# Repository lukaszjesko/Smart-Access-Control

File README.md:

# Smart Access Control

A door lock controller on my own PCB. To open the door you need the right RFID card
and the right 4-digit PIN. An Arduino Nano checks both and switches a 12 V door strike
through a relay.

| KiCad 3D render | Assembled board |
|---|---|
|  |  |

This is the first PCB I designed and ordered. I drew v1.0 in KiCad, found a lot of
mistakes during a review, fixed them in v1.1 and ordered v1.1 from JLCPCB.

## What's on the board

Arduino Nano, MFRC522 RFID reader (as a module on a header), 4x4 keypad, 16x2 LCD over
I2C, relay module, buzzer and two LEDs.

The firmware is a simple state machine: wait for a card, wait for the PIN, open or deny,
then back to waiting.

| Routing (ground pour hidden) | All copper layers |
|---|---|
|  |  |

*Red = top copper, blue = bottom copper. On the left the ground pour is hidden so
the tracks are visible.*

Schematic as PDF: [docs/schematic_v1.1.pdf](docs/schematic_v1.1.pdf).
KiCad project: [Zamek_RFID_Hardware/](Zamek_RFID_Hardware/Zamek_RFID_Hardware).

## Mistakes in v1.0 that I fixed in v1.1

- Both LEDs were wired backwards, so they could never light up.
- There were no decoupling capacitors. I had a supply dip that I worked around in
  firmware, but the real problem was in hardware.
- Every track was 0.25 mm, including power. Now power tracks are 0.6 mm and there is
  a ground pour on both layers.
- The Nano sent 5 V signals into the 3.3 V RFID reader. Now there are 1k/2k resistor
  dividers on MOSI, SCK and SS.
- The buzzer was driven straight from a pin. Now it goes through a BC547 transistor
  with a flyback diode.
- No mounting holes and no test points. Now there are four M3 holes and test points on
  5 V, 3.3 V and GND.

## A bug I liked

The relay module is active LOW, so at power-up the door opened for a split second
before the program set the pin. Writing HIGH to the pin before `pinMode()` fixed it.

## Not done yet

- Assemble and test v1.1
- Firmware: replace `String` with a `char` buffer, replace `delay()` with `millis()`,
  lock the keypad after 5 wrong PINs
- Security: only the card UID is checked, and a UID can be copied to a cheap card.
  The PIN is stored in the firmware as plain text.

## Build

PlatformIO, target `nanoatmega328new`:

```bash
cp include/config.example.h include/config.h   # set your card UID and PIN
pio run --target upload
```

## License

Firmware: [MIT](LICENSE). Hardware: [CERN-OHL-S-2.0](LICENSE-HARDWARE).

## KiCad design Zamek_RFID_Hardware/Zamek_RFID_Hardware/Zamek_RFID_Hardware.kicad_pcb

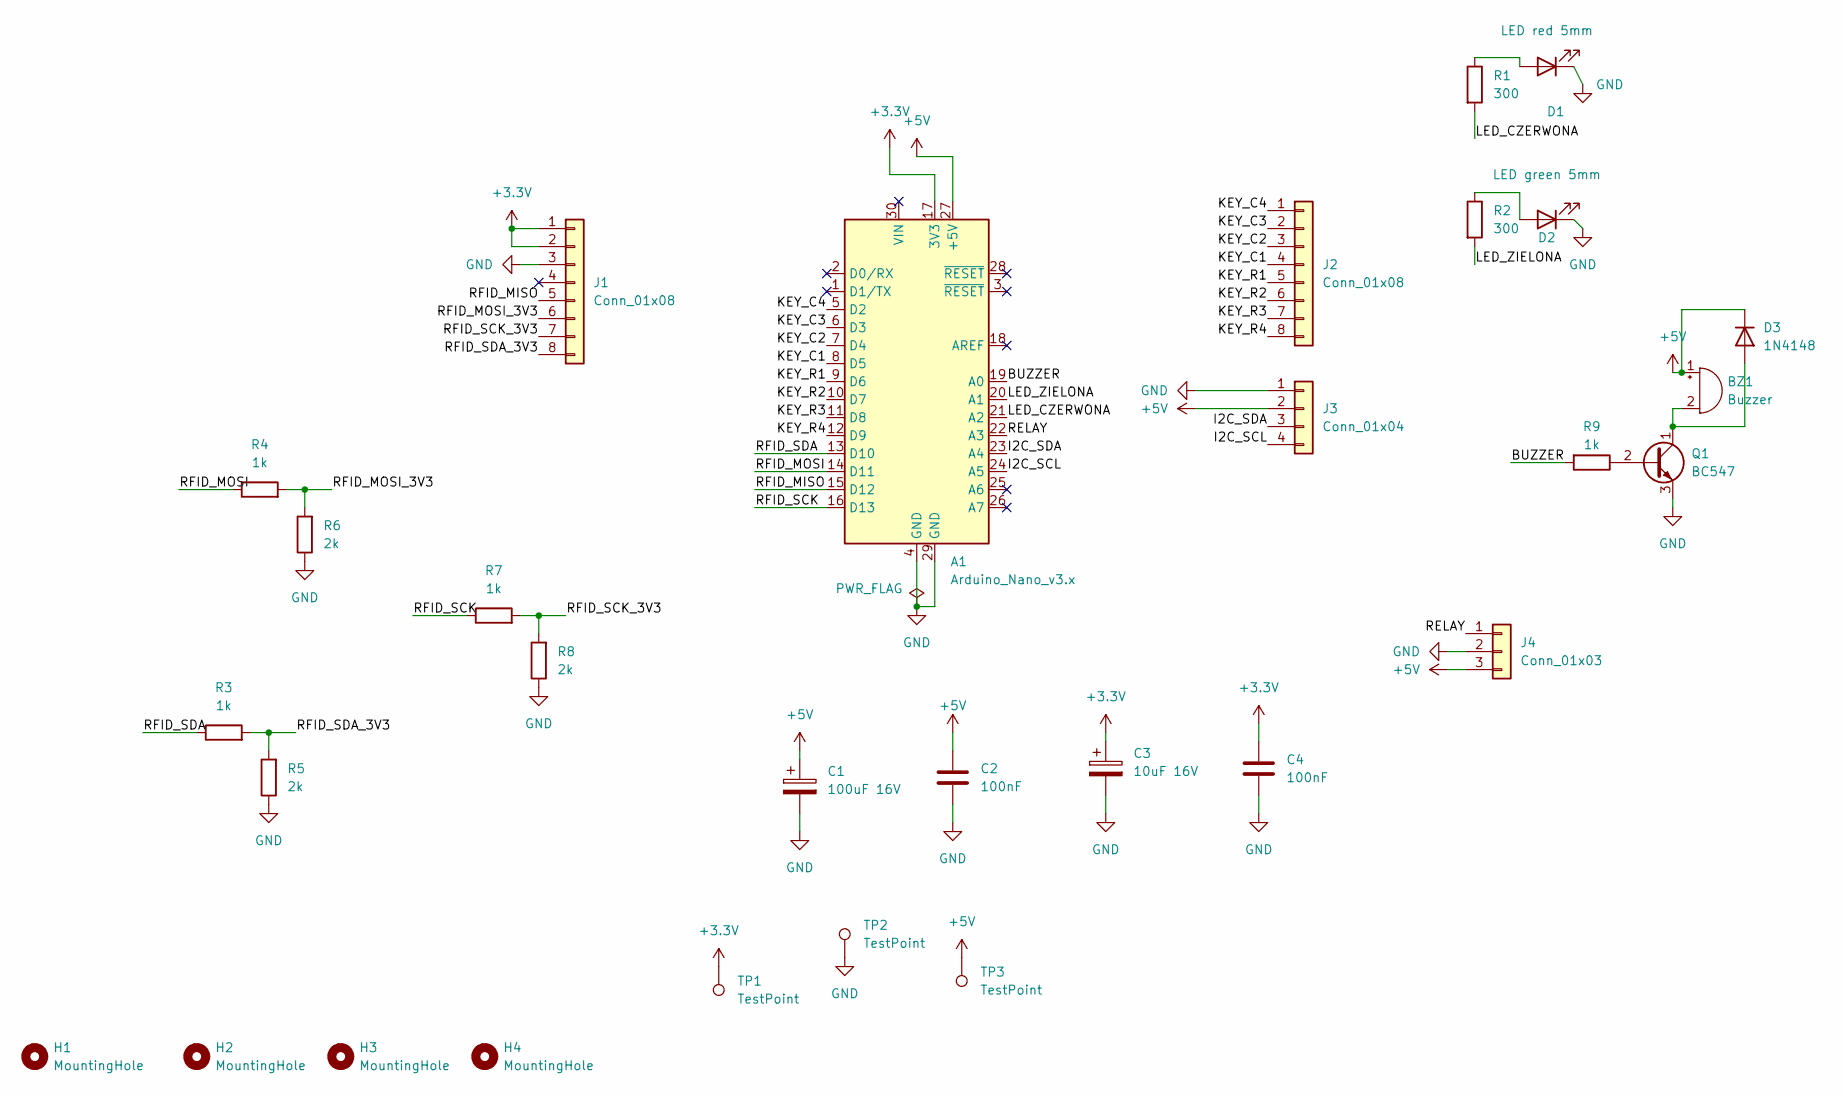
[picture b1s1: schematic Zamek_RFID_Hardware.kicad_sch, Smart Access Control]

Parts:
A1: Arduino_Nano_v3.x; Arduino_Nano
BZ1: Buzzer; Buzzer_12x9.5RM7.6
C1: 100uF 16V; CP_Radial_D6.3mm_P2.50mm
C2, C4: 100nF; C_Disc_D5.0mm_W2.5mm_P5.00mm
C3: 10uF 16V; CP_Radial_D5.0mm_P2.00mm
D1: LED red 5mm; LED_D5.0mm
D2: LED green 5mm; LED_D5.0mm
D3: 1N4148; D_DO-35_SOD27_P7.62mm_Horizontal
H1, H2, H3, H4: MountingHole; MountingHole_3.2mm_M3
J1, J2: Conn_01x08; PinHeader_1x08_P2.54mm_Vertical
J3: Conn_01x04; PinHeader_1x04_P2.54mm_Vertical
J4: Conn_01x03; PinHeader_1x03_P2.54mm_Vertical
Q1: BC547; TO-92_Inline
R1, R2: 300; R_Axial_DIN0207_L6.3mm_D2.5mm_P10.16mm_Horizontal
R3, R4, R7, R9: 1k; R_Axial_DIN0207_L6.3mm_D2.5mm_P10.16mm_Horizontal
R5, R6, R8: 2k; R_Axial_DIN0207_L6.3mm_D2.5mm_P10.16mm_Horizontal
TP1, TP2, TP3: TestPoint; TestPoint_THTPad_D2.0mm_Drill1.0mm

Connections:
+3.3V: A1.17 (3V3), C3.1, C4.1, J1.1, J1.2, TP1.1 (1_1)
+5V: A1.27 (+5V), BZ1.1 (+), C1.1, C2.1, D3.1 (K), J3.2, J4.3, TP3.1 (1_1)
/BUZZER: A1.19 (A0), R9.2
/I2C_SCL: A1.24 (A5), J3.4
/I2C_SDA: A1.23 (A4), J3.3
/KEY_C1: A1.8 (D5), J2.4
/KEY_C2: A1.7 (D4), J2.3
/KEY_C3: A1.6 (D3), J2.2
/KEY_C4: A1.5 (D2), J2.1
/KEY_R1: A1.9 (D6), J2.5
/KEY_R2: A1.10 (D7), J2.6
/KEY_R3: A1.11 (D8), J2.7
/KEY_R4: A1.12 (D9), J2.8
/LED_CZERWONA: A1.21 (A2), R1.2
/LED_ZIELONA: A1.20 (A1), R2.2
/RELAY: A1.22 (A3), J4.1
/RFID_MISO: A1.15 (D12), J1.5
/RFID_MOSI: A1.14 (D11), R4.1
/RFID_MOSI_3V3: J1.6, R4.2, R6.2
/RFID_SCK: A1.16 (D13), R7.1
/RFID_SCK_3V3: J1.7, R7.2, R8.2
/RFID_SDA: A1.13 (D10), R3.1
/RFID_SDA_3V3: J1.8, R3.2, R5.2
GND: A1.4 (GND), A1.29 (GND), C1.2, C2.2, C3.2, C4.2, D1.1 (K), D2.1 (K), J1.3, J3.1, J4.2, Q1.3 (E), R5.1, R6.1, R8.1, TP2.1 (1_1)
unnamed: BZ1.2 (-), D3.2 (A), Q1.1 (C)
unnamed: D1.2 (A), R1.1
unnamed: D2.2 (A), R2.1
unnamed: Q1.2 (B), R9.1

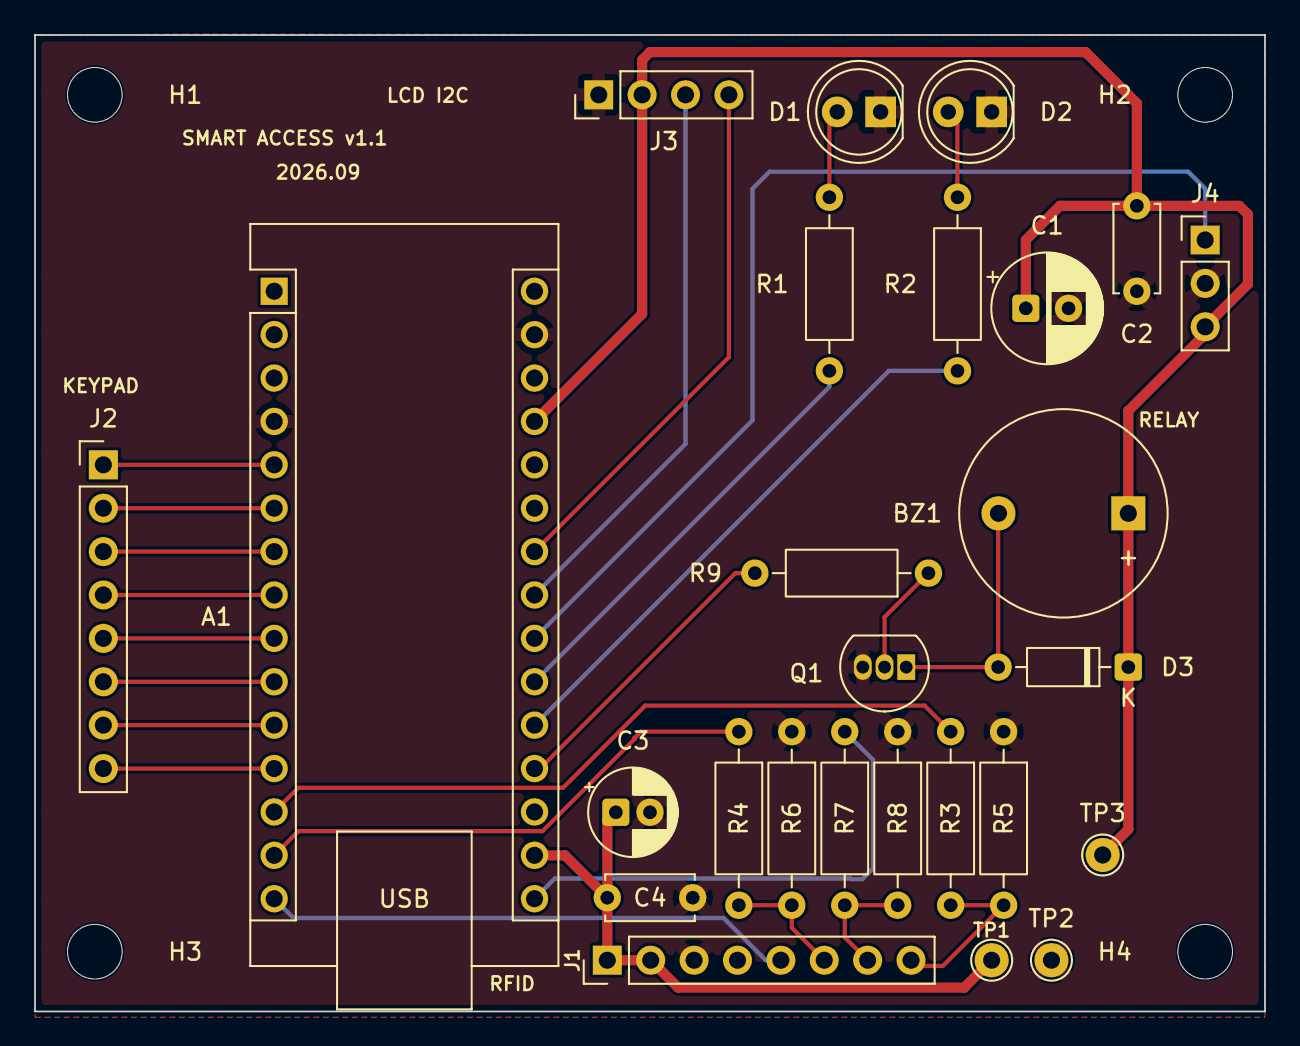
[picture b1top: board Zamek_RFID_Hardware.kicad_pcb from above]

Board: 2 copper layers, 72.0 x 57.2 mm, 30 parts (0 on the bottom side), 28 nets.

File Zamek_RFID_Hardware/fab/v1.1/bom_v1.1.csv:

"Reference","Value","Datasheet","Footprint","Qty","DNP"
"A1","Arduino_Nano_v3.x","http://www.mouser.com/pdfdocs/Gravitech_Arduino_Nano3_0.pdf","Module:Arduino_Nano","1",""
"BZ1","Buzzer","","Buzzer_Beeper:Buzzer_12x9.5RM7.6","1",""
"C1","100uF 16V","","Capacitor_THT:CP_Radial_D6.3mm_P2.50mm","1",""
"C2,C4","100nF","","Capacitor_THT:C_Disc_D5.0mm_W2.5mm_P5.00mm","2",""
"C3","10uF 16V","","Capacitor_THT:CP_Radial_D5.0mm_P2.00mm","1",""
"D1","LED red 5mm","","LED_THT:LED_D5.0mm","1",""
"D2","LED green 5mm","","LED_THT:LED_D5.0mm","1",""
"D3","1N4148","https://assets.nexperia.com/documents/data-sheet/1N4148_1N4448.pdf","Diode_THT:D_DO-35_SOD27_P7.62mm_Horizontal","1",""
"J1,J2","Conn_01x08","","Connector_PinHeader_2.54mm:PinHeader_1x08_P2.54mm_Vertical","2",""
"J3","Conn_01x04","","Connector_PinHeader_2.54mm:PinHeader_1x04_P2.54mm_Vertical","1",""
"J4","Conn_01x03","","Connector_PinHeader_2.54mm:PinHeader_1x03_P2.54mm_Vertical","1",""
"Q1","BC547","https://www.onsemi.com/pub/Collateral/BC550-D.pdf","Package_TO_SOT_THT:TO-92_Inline","1",""
"R1","300","","Resistor_THT:R_Axial_DIN0207_L6.3mm_D2.5mm_P10.16mm_Horizontal","1",""
"R2","200","","Resistor_THT:R_Axial_DIN0207_L6.3mm_D2.5mm_P10.16mm_Horizontal","1",""
"R3,R4,R7,R9","1k","","Resistor_THT:R_Axial_DIN0207_L6.3mm_D2.5mm_P10.16mm_Horizontal","4",""
"R5,R6,R8","2k","","Resistor_THT:R_Axial_DIN0207_L6.3mm_D2.5mm_P10.16mm_Horizontal","3",""

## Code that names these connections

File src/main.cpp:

#include <Arduino.h>
#include <Wire.h>
#include <Keypad.h>
#include <LiquidCrystal_I2C.h>
#include <SPI.h>
#include <MFRC522.h>
#include "config.h"

#define SDA_PIN 10
#define RST_PIN -1

MFRC522 rfid(SDA_PIN, RST_PIN);
LiquidCrystal_I2C lcd(0x27, 16, 2); 


const byte ROWS = 4; 
const byte COLS = 4;

byte rowPins[ROWS] = {6,7,8,9};
byte colPins[COLS] = {5,4,3,2};

char keys[ROWS][COLS] = {
 {'1','2','3','A'},
 {'4','5','6','B'},
 {'7','8','9','C'},
 {'*','0','#','D'}
 };

 enum StanSystemu {
    CZEKAM_NA_PIN,
    WPISYWANIE_PINU,
    ZAAKCEPTOWANY,
    ODRZUCONY,
    CZEKAM_NA_KARTE
 };

 StanSystemu obecnyStan = CZEKAM_NA_KARTE;


 String wpisanyPin = "";
 const byte PIN_BUZZER = A0;
 const byte PIN_LED_ZIELONA = A1;
 const byte PIN_LED_CZERWONA = A2;
 const byte PIN_PRZEKAZNIK = A3;


 
 Keypad keypad = Keypad(makeKeymap(keys), rowPins, colPins, ROWS, COLS);

void pokazLinie(byte wiersz, const char* tekst) {
  lcd.setCursor(0, wiersz);
  lcd.print("                "); 
  lcd.setCursor(0, wiersz);
  lcd.print(tekst);
}

void setup() {
  
  pinMode(PIN_BUZZER, OUTPUT);
  pinMode(PIN_LED_ZIELONA, OUTPUT);
  pinMode(PIN_LED_CZERWONA, OUTPUT);
  pinMode(PIN_PRZEKAZNIK, OUTPUT);

  digitalWrite(PIN_PRZEKAZNIK, HIGH);
  digitalWrite(PIN_BUZZER, LOW);
  digitalWrite(PIN_LED_CZERWONA, HIGH);
  digitalWrite(PIN_LED_ZIELONA, LOW);

  SPI.begin();
  rfid.PCD_Init();
  Serial.begin(115200);

  lcd.init();
  lcd.backlight();
  lcd.setCursor(0, 0);
  lcd.print("System gotowy");
  lcd.setCursor(0, 1);
  lcd.print("Zbliz karte: ");
}

void loop() {
  char key = keypad.getKey();
  
  switch(obecnyStan){
    case CZEKAM_NA_PIN:
      if (key){
        wpisanyPin+= key;
        lcd.clear();
        lcd.setCursor(0, 0);
        lcd.print("Wprowadz PIN:");
        lcd.setCursor(0, 1);
        lcd.print("*");
        obecnyStan = WPISYWANIE_PINU;

      }
    break;

    case WPISYWANIE_PINU:
      if(key){
        wpisanyPin += key;
        lcd.print("*");

        if (wpisanyPin.length() == 4){
          lcd.clear();
          lcd.setCursor(0, 0);
          lcd.print("Weryfikacja...");

          if (wpisanyPin == tajnyPin){
            obecnyStan = ZAAKCEPTOWANY;
          }else{
            obecnyStan = ODRZUCONY;
          }
        
        }
      }
    break;

    case CZEKAM_NA_KARTE:
      
      if (rfid.PICC_IsNewCardPresent() && rfid.PICC_ReadCardSerial()) {      
        String odczytaneUID = "";
        for (byte i = 0; i < rfid.uid.size; i++) {         
          odczytaneUID.concat(String(rfid.uid.uidByte[i] < 0x10 ? " 0" : " "));
          odczytaneUID.concat(String(rfid.uid.uidByte[i], HEX));
        }
        odczytaneUID.toUpperCase(); 
        if (odczytaneUID == dozwolonaKarta) { 
          
        Serial.println(odczytaneUID);

        rfid.PICC_HaltA();
        digitalWrite(PIN_BUZZER, HIGH); delay(100); digitalWrite(PIN_BUZZER, LOW); 
        lcd.clear();
        lcd.setCursor(0, 0);
        lcd.print("Karta OK");
        lcd.setCursor(0, 1);
        lcd.print("Wprowadz PIN:");
        obecnyStan = CZEKAM_NA_PIN; 
      }
      else{
        Serial.println("Nieznana karta: " + odczytaneUID);
        rfid.PICC_HaltA();
        lcd.clear();
        lcd.setCursor(0, 0);
        lcd.print("Odmowa dostepu");
        lcd.setCursor(0, 1);
        lcd.print("Nieznana karta");

        digitalWrite(PIN_BUZZER, HIGH);
        delay(2000);
        digitalWrite(PIN_BUZZER, LOW);

        lcd.clear();
        lcd.setCursor(0, 0);
        lcd.print("System gotowy");
        lcd.setCursor(0, 1);
        lcd.print("Zbliz karte: ");
        
      }
    }
    break;

    case ZAAKCEPTOWANY:
      lcd.clear();
      lcd.setCursor(0, 0);
      lcd.print("Dostep przyznany"); 
      lcd.setCursor(0, 1);
      lcd.print("Zamek otwarty");
      
      digitalWrite(PIN_LED_CZERWONA, LOW);
      digitalWrite(PIN_LED_ZIELONA, HIGH);
      digitalWrite(PIN_PRZEKAZNIK, LOW);
      delay(3000);
      digitalWrite(PIN_PRZEKAZNIK, HIGH);
      digitalWrite(PIN_LED_ZIELONA, LOW);
      digitalWrite(PIN_LED_CZERWONA, HIGH);
      
      lcd.clear();
      lcd.setCursor(0, 0);
      lcd.print("System gotowy");
      lcd.setCursor(0, 1);
      lcd.print("Zbliz karte: ");

      wpisanyPin = "";
      obecnyStan = CZEKAM_NA_KARTE;
    break;

    case ODRZUCONY:
      lcd.clear();
      lcd.setCursor(0, 0);
      lcd.print("Odmowa dostepu!");
      lcd.setCursor(0, 1);
      lcd.print("Bledny PIN!");
      
      digitalWrite(PIN_BUZZER, HIGH);
      delay(2000);
      digitalWrite(PIN_BUZZER, LOW);
      
      lcd.clear();
      lcd.setCursor(0, 0);
      lcd.print("System gotowy");
      lcd.setCursor(0, 1);
      lcd.print("Zbliz karte: ");
      
      wpisanyPin = "";
      obecnyStan = CZEKAM_NA_KARTE;
    break;
  }
}
